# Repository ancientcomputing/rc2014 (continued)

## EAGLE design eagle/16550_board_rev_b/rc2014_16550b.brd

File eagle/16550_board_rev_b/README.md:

16550 UART Board Rev B
<p>
This is the Rev B version of the 16550 UART Board for the RC2014.
<p>
The top 3 changes are:
<br>- Use of port addresses C0H-FFH to avoid collision with the default 68B50 UART
<br>- Use of 74HCT03 open collector gates, particularly to drive the /INT signal line so that it can be shared with other devices that also drive the interrupt line.
<br>- Availability of the 16550's OP1 and OP2 lines to a pin header for general use e.g. to generate an audio signal or page switch RAM/ROM etc.
<p>
This design has been tested with a PC16550CN.
<p>
PCBs are available from OSH Park at:
<p>
<a href="https://www.oshpark.com/shared_projects/zJddwYAf"></img></a>

<p>
A BIOS will be available soon.

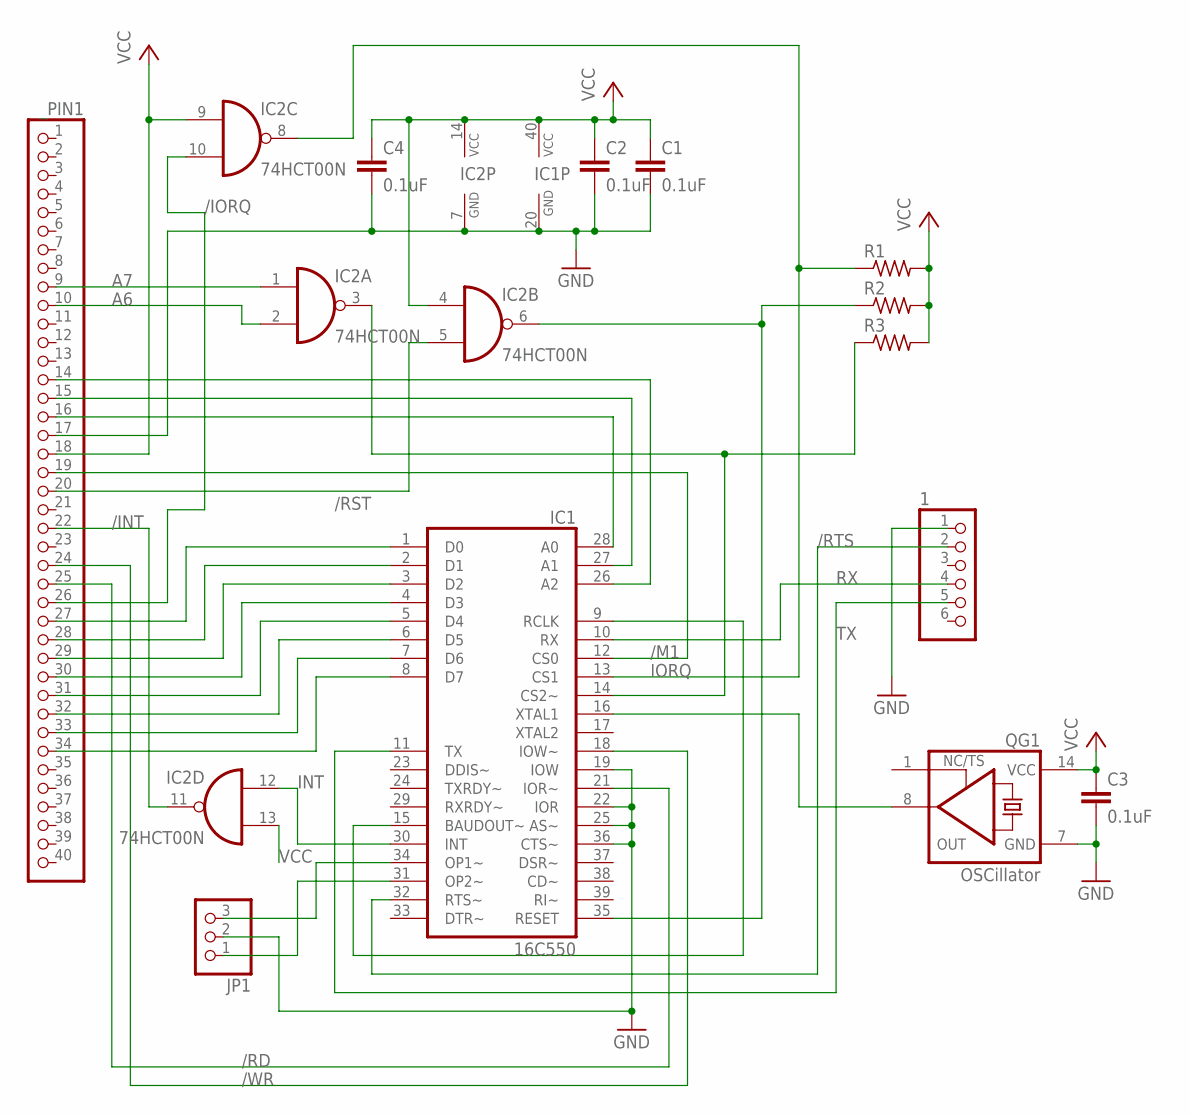
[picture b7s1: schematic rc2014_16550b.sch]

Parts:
1: PINHD-1X6; 1X06
C1, C2, C3, C4: 0.1uF; C050-024X044
IC1: 16C550; DIL40
IC2: 74HCT00N; DIL14
JP1: PINHD-1X3; 1X03
QG1: OSCillator; DIL14S
R1, R2, R3: R-US_0207/10; 0207/10
_PIN1: PINHD-1X40; 1X40

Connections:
/CS2: IC1.14 (CS2~), IC2.3 (O), R3.1
/INT: IC2.11 (O), _PIN1.22
/IORQ: IC2.10 (I1), _PIN1.26
/M1: IC1.12 (CS0), _PIN1.19
/RD: IC1.21 (IOR~), _PIN1.25
/RST: IC2.5 (I1), _PIN1.20
/RTS: 1.2, IC1.32 (RTS~)
/WR: IC1.18 (IOW~), _PIN1.24
A0: IC1.28 (A0), _PIN1.16
A1: IC1.27 (A1), _PIN1.15
A2: IC1.26 (A2), _PIN1.14
A6: IC2.2 (I1), _PIN1.10
A7: IC2.1 (I0), _PIN1.9
D0: IC1.1 (D0), _PIN1.27
D1: IC1.2 (D1), _PIN1.28
D2: IC1.3 (D2), _PIN1.29
D3: IC1.4 (D3), _PIN1.30
D4: IC1.5 (D4), _PIN1.31
D5: IC1.6 (D5), _PIN1.32
D6: IC1.7 (D6), _PIN1.33
D7: IC1.8 (D7), _PIN1.34
GND: 1.1, C1.2, C2.2, C3.2, C4.2, IC1.19 (IOW), IC1.20 (GND), IC1.22 (IOR), IC1.25 (AS~), IC1.36 (CTS~), IC2.7 (GND), JP1.2, QG1.7 (GND), _PIN1.17
INT: IC1.30 (INT), IC2.12 (I0)
IORQ: IC1.13 (CS1), IC2.8 (O), R1.1
unnamed: IC1.34 (OP1~), JP1.3
unnamed: IC1.31 (OP2~), JP1.1
unnamed: IC1.9 (RCLK), IC1.15 (BAUDOUT~)
OSC: IC1.16 (XTAL1), QG1.8 (OUT)
RESET: IC1.35 (RESET), IC2.6 (O), R2.1
RX: 1.4, IC1.10 (RX)
TX: 1.5, IC1.11 (TX)
VCC: C1.1, C2.1, C3.1, C4.1, IC1.40 (VCC), IC2.4 (I0), IC2.9 (I0), IC2.13 (I1), IC2.14 (VCC), QG1.14 (VCC), R1.2, R2.2, R3.2, _PIN1.18

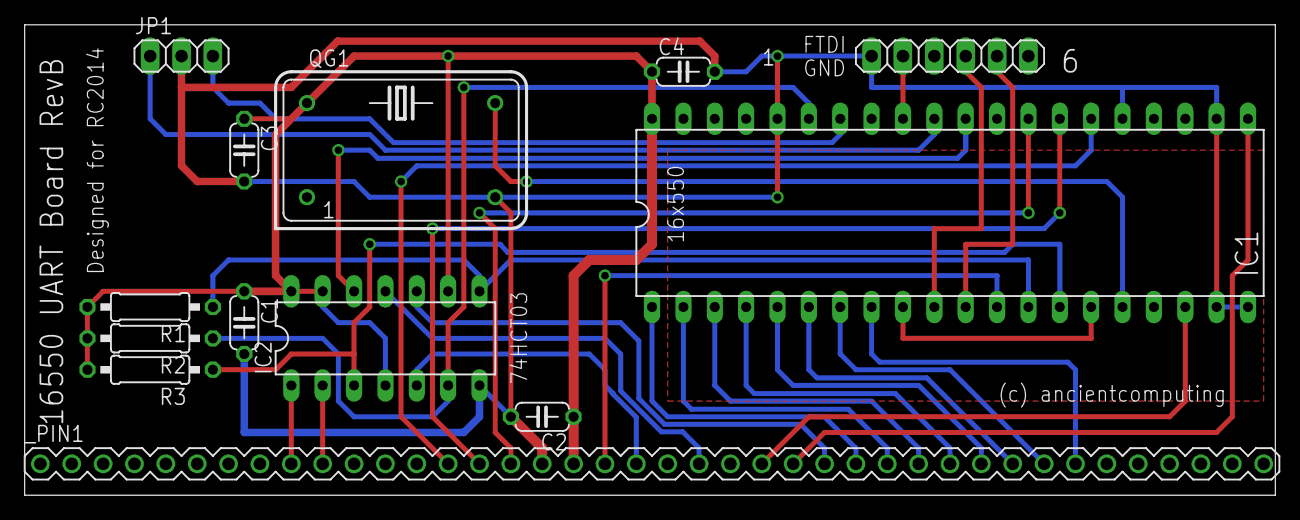
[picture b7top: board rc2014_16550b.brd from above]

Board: 2 copper layers, 101.3 x 38.1 mm, 13 parts (0 on the bottom side), 32 nets.

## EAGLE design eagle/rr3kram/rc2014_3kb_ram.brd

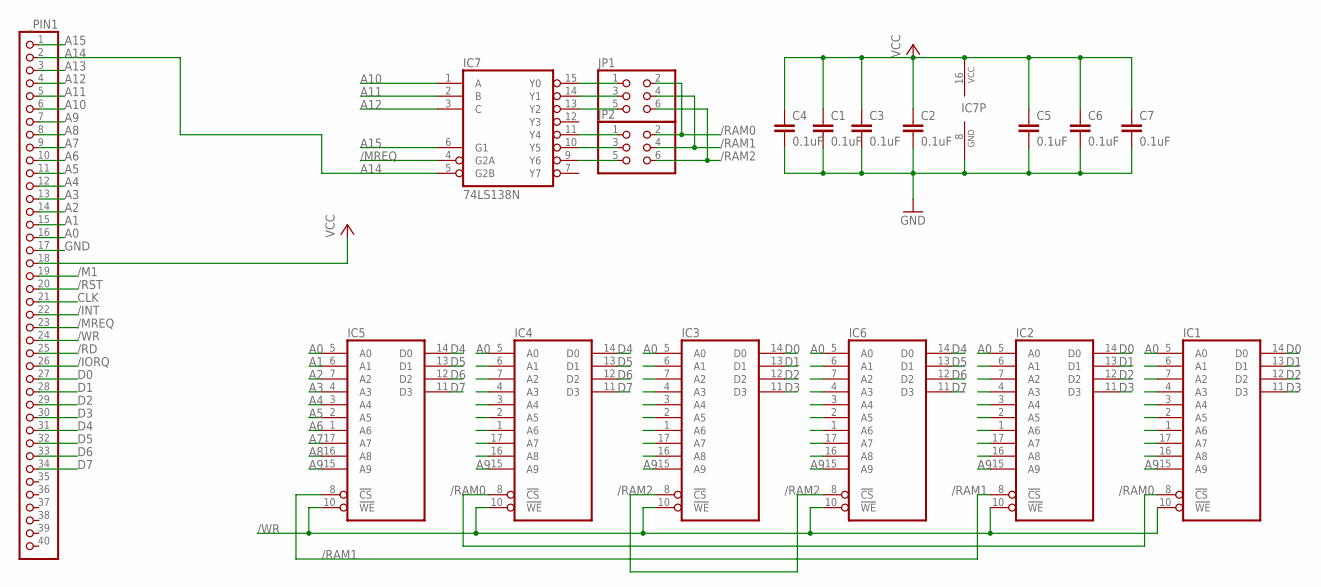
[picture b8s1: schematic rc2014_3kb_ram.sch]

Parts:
C1, C2, C3, C4, C5, C6, C7: 0.1uF; C050-024X044
IC1, IC2, IC3, IC4, IC5, IC6: 2114; DIL18
IC7: 74LS138N; DIL16
JP1, JP2: PINHD-2X3; 2X03
_PIN1: PINHD-1X40; 1X40

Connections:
/INT: _PIN1.22
/IORQ: _PIN1.26
/M1: _PIN1.19
/MREQ: IC7.4 (G2A), _PIN1.23
/RAM0: IC1.8 (!CS), IC4.8 (!CS), JP1.2, JP2.2
/RAM1: IC2.8 (!CS), IC5.8 (!CS), JP1.4, JP2.4
/RAM2: IC3.8 (!CS), IC6.8 (!CS), JP1.6, JP2.6
/RD: _PIN1.25
/RST: _PIN1.20
/WR: IC1.10 (!WE), IC2.10 (!WE), IC3.10 (!WE), IC4.10 (!WE), IC5.10 (!WE), IC6.10 (!WE), _PIN1.24
A0: IC1.5 (A0), IC2.5 (A0), IC3.5 (A0), IC4.5 (A0), IC5.5 (A0), IC6.5 (A0), _PIN1.16
A1: IC1.6 (A1), IC2.6 (A1), IC3.6 (A1), IC4.6 (A1), IC5.6 (A1), IC6.6 (A1), _PIN1.15
A2: IC1.7 (A2), IC2.7 (A2), IC3.7 (A2), IC4.7 (A2), IC5.7 (A2), IC6.7 (A2), _PIN1.14
A3: IC1.4 (A3), IC2.4 (A3), IC3.4 (A3), IC4.4 (A3), IC5.4 (A3), IC6.4 (A3), _PIN1.13
A4: IC1.3 (A4), IC2.3 (A4), IC3.3 (A4), IC4.3 (A4), IC5.3 (A4), IC6.3 (A4), _PIN1.12
A5: IC1.2 (A5), IC2.2 (A5), IC3.2 (A5), IC4.2 (A5), IC5.2 (A5), IC6.2 (A5), _PIN1.11
A6: IC1.1 (A6), IC2.1 (A6), IC3.1 (A6), IC4.1 (A6), IC5.1 (A6), IC6.1 (A6), _PIN1.10
A7: IC1.17 (A7), IC2.17 (A7), IC3.17 (A7), IC4.17 (A7), IC5.17 (A7), IC6.17 (A7), _PIN1.9
A8: IC1.16 (A8), IC2.16 (A8), IC3.16 (A8), IC4.16 (A8), IC5.16 (A8), IC6.16 (A8), _PIN1.8
A9: IC1.15 (A9), IC2.15 (A9), IC3.15 (A9), IC4.15 (A9), IC5.15 (A9), IC6.15 (A9), _PIN1.7
A10: IC7.1 (A), _PIN1.6
A11: IC7.2 (B), _PIN1.5
A12: IC7.3 (C), _PIN1.4
A13: _PIN1.3
A14: IC7.5 (G2B), _PIN1.2
A15: IC7.6 (G1), _PIN1.1
CLK: _PIN1.21
D0: IC1.14 (D0), IC2.14 (D0), IC3.14 (D0), _PIN1.27
D1: IC1.13 (D1), IC2.13 (D1), IC3.13 (D1), _PIN1.28
D2: IC1.12 (D2), IC2.12 (D2), IC3.12 (D2), _PIN1.29
D3: IC1.11 (D3), IC2.11 (D3), IC3.11 (D3), _PIN1.30
D4: IC4.14 (D0), IC5.14 (D0), IC6.14 (D0), _PIN1.31
D5: IC4.13 (D1), IC5.13 (D1), IC6.13 (D1), _PIN1.32
D6: IC4.12 (D2), IC5.12 (D2), IC6.12 (D2), _PIN1.33
D7: IC4.11 (D3), IC5.11 (D3), IC6.11 (D3), _PIN1.34
GND: C1.2, C2.2, C3.2, C4.2, C5.2, C6.2, C7.2, IC1.9 (GND), IC2.9 (GND), IC3.9 (GND), IC4.9 (GND), IC5.9 (GND), IC6.9 (GND), IC7.8 (GND), _PIN1.17
unnamed: IC7.15 (Y0), JP1.1
unnamed: IC7.14 (Y1), JP1.3
unnamed: IC7.13 (Y2), JP1.5
unnamed: IC7.11 (Y4), JP2.1
unnamed: IC7.10 (Y5), JP2.3
unnamed: IC7.9 (Y6), JP2.5
VCC: C1.1, C2.1, C3.1, C4.1, C5.1, C6.1, C7.1, IC1.18 (VCC), IC2.18 (VCC), IC3.18 (VCC), IC4.18 (VCC), IC5.18 (VCC), IC6.18 (VCC), IC7.16 (VCC), _PIN1.18

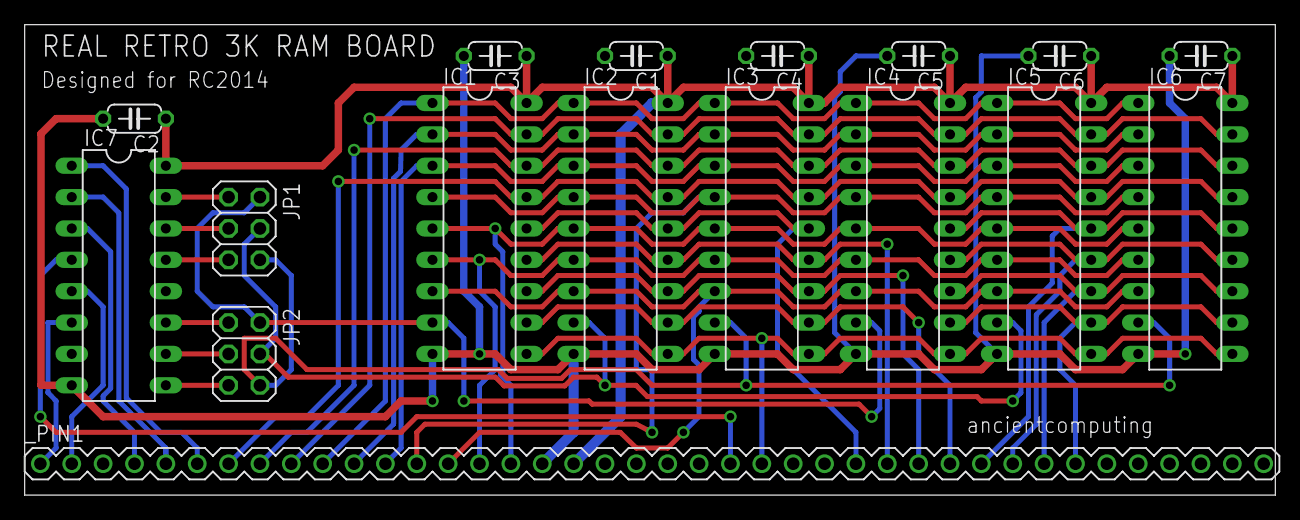
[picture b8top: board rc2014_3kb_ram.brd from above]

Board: 2 copper layers, 101.3 x 38.1 mm, 17 parts (0 on the bottom side), 36 nets.

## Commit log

2017-03-04 test
2017-03-04 initial
2017-03-06 added more comments for clarity
2017-03-06 more comments
2017-03-07 fix Intel HEX file upload
2017-03-07 fix startup string
2017-03-11 Clean up code and comments
2017-03-11 Update the README and upload a new mon.rom that contains the latest version of the RC2014 monitor.
2017-03-11 Fix typos
2017-03-12 New Monitor/Debugger features and general clean up
2017-03-12 Fix typo
2017-03-13 Add blog URL to READMEwq
2017-03-13 Typos
2017-03-15 Further optimization of the Monitor/Debugger
2017-03-15 Typos in the README.mdwq
2017-03-16 Version 0.5.1
2017-03-22 Version 0.6.0 with inline disassembler
2017-03-22 Add romit2.sh to build monitor/debugger binary
2017-03-25 User Guide
2017-03-25 v0.6.1 Preserve IFF state after breakpoints
2017-03-26 Monitor+BASIC in one rom
2017-03-26 misc changes
2017-03-27 Tweak README.md
2017-04-01 Update doc
2017-04-02 Update manual for hex load
2017-04-08 Version 0.7.0 includes 255-byte serial receive buffer and other tweaks.
2017-04-08 The breakpoint register locations in memory have changed.
2017-04-09 Eagle files for RC2014 add-on boards
2017-04-10 Move a bunch of code from int32K.asm to mon32K.asm. v0.7.1
2017-04-10 Fix wiring issue with template
2017-04-16 Added 16550 board and new CPU board
2017-04-16 Added LICENSE and updated README
2017-04-18 8085 CPU Board
2017-04-20 NSC800 library for Eagle
2017-04-22 Real Retro 3KB RAM board
2017-04-22 screenshot of board
2017-04-23 Add support for the Z80 SIO
2017-04-23 Add pdf of schematic
2017-04-24 replace png with pdf
2017-04-25 Add support for 16550/16C550 UART with the 16x550 UART card
2017-04-25 Add link to OSH Park to order the 16x550 UART card
2017-04-25 Update README for copyright and license
2017-04-26 Replace png with higher res pdf
2017-04-26 Add signal labels and PDF of schematic
2017-04-26 NSC800 CPU board
2017-04-26 Add png of board
2017-04-29 Clean up stencils
2017-04-29 Update resistor values
2017-04-29 Add OSH Park order link
2017-04-29 Fixed wiring error on PCB
2017-04-30 Clean up, add CLK
2017-05-09 Fix missing A1, A0 lines
2017-05-09 Tested
2017-05-11 Add 16550 UART Board Rev B
2017-05-11 Update README.md for the Real Retro 3KB RAM board
2017-05-11 Formatting
2017-05-12 Update BIOS to support the 16550 Rev B board
2017-05-12 Correctly identify 74LS03
2017-05-12 Update 8085 board includeing OSH Park link
2017-05-12 Correct 20pF capacitor value for <4MHz crystal
2017-05-14 Add 8085 Monitor
2017-05-14 Added support for I and O instructions for 8080/8085
2017-05-14 Real Retro UART Board
2017-05-17 Add BIOS and Monitor ROM for Real Retro UART Board
2017-05-20 Simple ROM RAM board for the RC2014
2017-05-20 IMSAI 8K BASIC
2017-05-20 IMSAI 8K BASIC - add Udo Munk changes
2017-05-28 6502 Monitor program
2017-05-28 6502 CPU Board
2017-05-29 BIOS for 16C550 UART
2017-05-29 Start Monitor/Debugger at
2017-05-29 Fix bug with ? command
2017-06-01 Squeeze Monitor into top 1K, use common function names for UART for compatibility
2017-06-01 Clarify where the Monitor is located in the 32KB ROM images
2017-06-01 Initial checkin of EhBASIC
2017-06-01 Add Ross Archer webpage
2017-06-02 Fix instability with upload
2017-06-02 Update README.md
    JP1 should be shorted to GND when NOT using the WDC chip. On the WDC chip, VPB (Vector Pull (Bar)) is an output that should be disconnected.
2017-06-03 6850 ACIA support
2017-06-03 Version 0.1.2 with bug fixes and better alignment with Z80 monitor debugger user interface
2017-06-04 More bug fixes and optimizations. Added U as an explicit upload command
2017-06-04 Consolidate error handling for upload.asm
2017-06-04 Working version with Daryl's latest patch
2017-06-05 Add jumps for cold and warm start and SYS command to jump to Monitor
2017-06-06 Add support for the RC2014 Serial IO board
2017-06-10 Resume from breakpoint feature
2017-06-10 Combo Monitor and EhBASIC ROM image
2017-06-18 Update the readme files
2017-06-18 Build scripts for combo rom image
2017-06-18 Clarify that the Monitor-EhBASIC rom is for use with 16550
2017-06-18 Bring in ROM images for other UARTs
2017-06-20 6502 CPU Board RevB
2017-06-24 mon6502 images for different ROM sizes
2017-06-24 16550 UART Board RevC
2017-06-25 Part nos and picture
2017-06-25 OSH Park order link
2017-07-01 Forgot to update fitnfinish
2017-07-01 Add console input buffer
2017-07-01 Add console input buffer with IRQ
2017-07-02 Optimize ZP usage
2017-07-02 65xx component library with 6532
2017-07-02 Initial check-in for 6522 sample code
2017-07-03 6522 VIA Board for RC2014
2017-07-03 Clean up
2017-07-03 Re-organize source folders
2017-07-03 Re-organize rom folders
2017-07-03 Test interleaving interrupts
2017-07-04 Initial checkin of MicroChess
2017-07-05 Add picture
2017-07-05 Correct timer value for 10ms tick
2017-07-05 ANSI VT100 terminal routines
2017-07-05 Tweaks to use ANSI VT100 library and general clean up
2017-07-05 Typoswq
2017-07-07 Added music routines
2017-07-08 Use RAM based vectors for console IO
2017-07-08 Add links to Tindie
2017-07-08 Add BIOS support for 6551 ACIA
2017-07-08 Add support for 16C750 UART with 64char FIFO
2017-07-08 Add support for 6551 ACIA
2017-07-09 move stuff around
2017-07-09 Add support for 6551 IRQ mode
2017-07-09 Script to build monitor with BASIC
2018-05-06 6809 CPU board
2018-05-06 6809 bringup code
2018-05-12 Update test routines and hex file
2018-05-12 Fixed typos, add speaker driver schematic and update README with more instructions
2018-05-12 PDF versions of the schematic and board layout
2018-05-12 Picture of the 6522 board with driver and mini-speaker
